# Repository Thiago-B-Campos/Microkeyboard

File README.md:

# Microkeyboard Hackpad

This is my hackpad project submission.

## Overview
I am making a micro keyboard in the QWERTY standard. The goal is to have at least 12 keys, 1 OLED display, and 1 rotary encoder.

## Images

### Schematic

### PCB

### Case

### Case - Shell

### BOM:

- 11x Cherry MX Switches
- 1x XIAO RP2040
- 11x Keycaps
- 1x Alps EC11E Rotary Encoder/Switch
- 4x M3x16mm screws
- 1x 3D Printed Case (2 parts)

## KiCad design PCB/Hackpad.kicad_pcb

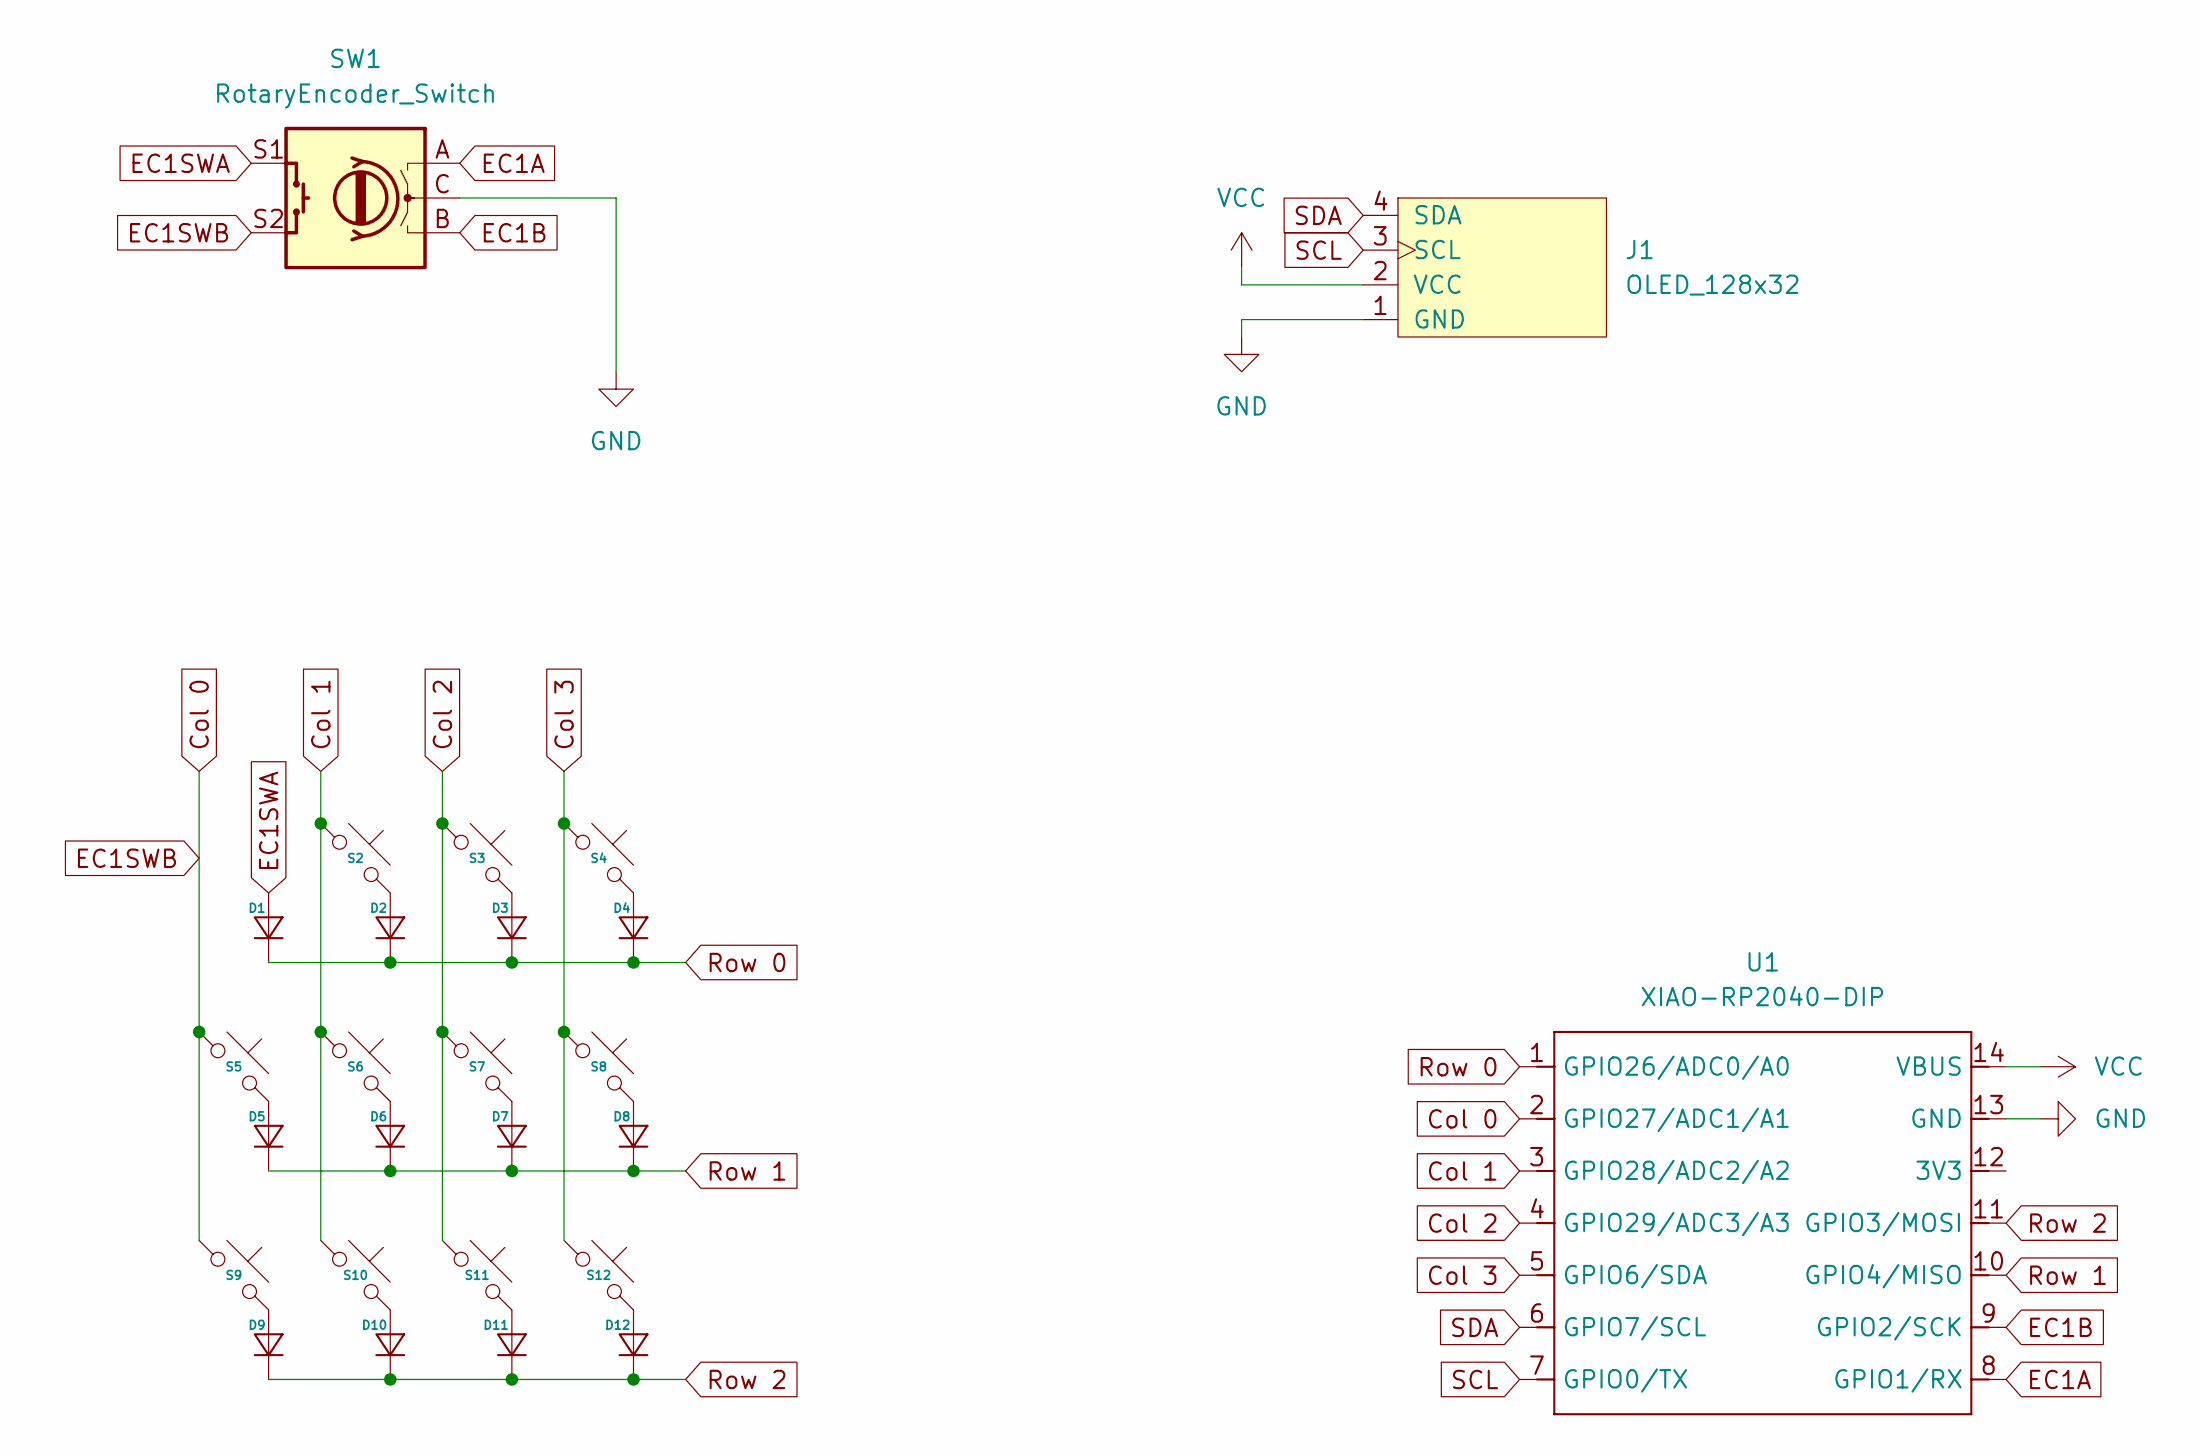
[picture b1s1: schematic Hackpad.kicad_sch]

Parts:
D1, D2, D3, D4, D5, D6, D7, D8, D9, D10, D11, D12: Diode_DO-35
J1: OLED_128x32
S2, S3, S4, S5, S6, S7, S8, S9, S10, S11, S12: SW_Cherry_MX_PCB_1.00u
SW1: RotaryEncoder_Switch; RotaryEncoder_Alps_EC11E-Switch_Vertical_H20mm
U1: XIAO-RP2040-DIP; Seeed_XIAO_RP2040

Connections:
Col 0: S5.1, S9.1, SW1.S2, U1.2 (GPIO27/ADC1/A1)
Col 1: S2.1, S6.1, S10.1, U1.3 (GPIO28/ADC2/A2)
Col 2: S3.1, S7.1, S11.1, U1.4 (GPIO29/ADC3/A3)
Col 3: S4.1, S8.1, S12.1, U1.5 (GPIO6/SDA)
EC1A: SW1.A, U1.8 (GPIO1/RX)
EC1B: SW1.B, U1.9 (GPIO2/SCK)
EC1SWA: D1.2 (A), SW1.S1
GND: J1.1 (GND), SW1.C, U1.13 (GND)
unnamed: D2.2 (A), S2.2
unnamed: D3.2 (A), S3.2
unnamed: D4.2 (A), S4.2
unnamed: D5.2 (A), S5.2
unnamed: D6.2 (A), S6.2
unnamed: D7.2 (A), S7.2
unnamed: D8.2 (A), S8.2
unnamed: D9.2 (A), S9.2
unnamed: D10.2 (A), S10.2
unnamed: D11.2 (A), S11.2
unnamed: D12.2 (A), S12.2
Row 0: D1.1 (K), D2.1 (K), D3.1 (K), D4.1 (K), U1.1 (GPIO26/ADC0/A0)
Row 1: D5.1 (K), D6.1 (K), D7.1 (K), D8.1 (K), U1.10 (GPIO4/MISO)
Row 2: D9.1 (K), D10.1 (K), D11.1 (K), D12.1 (K), U1.11 (GPIO3/MOSI)
SCL: J1.3 (SCL), U1.7 (GPIO0/TX)
SDA: J1.4 (SDA), U1.6 (GPIO7/SCL)
VCC: J1.2 (VCC), U1.14 (VBUS)

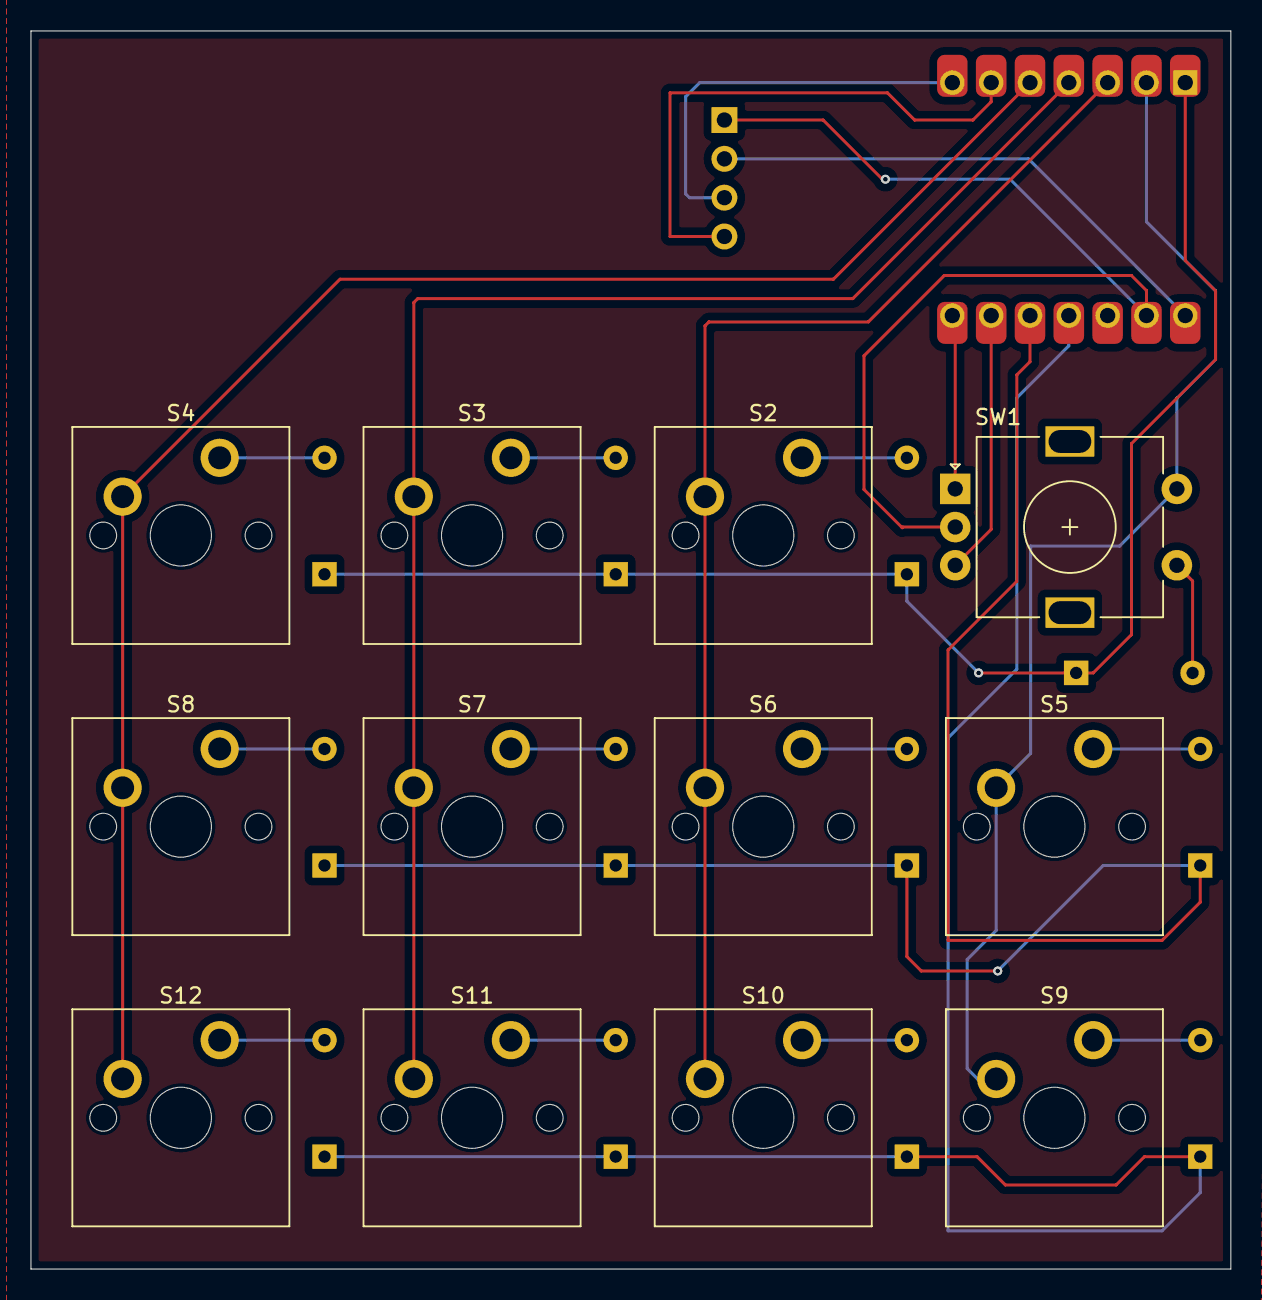
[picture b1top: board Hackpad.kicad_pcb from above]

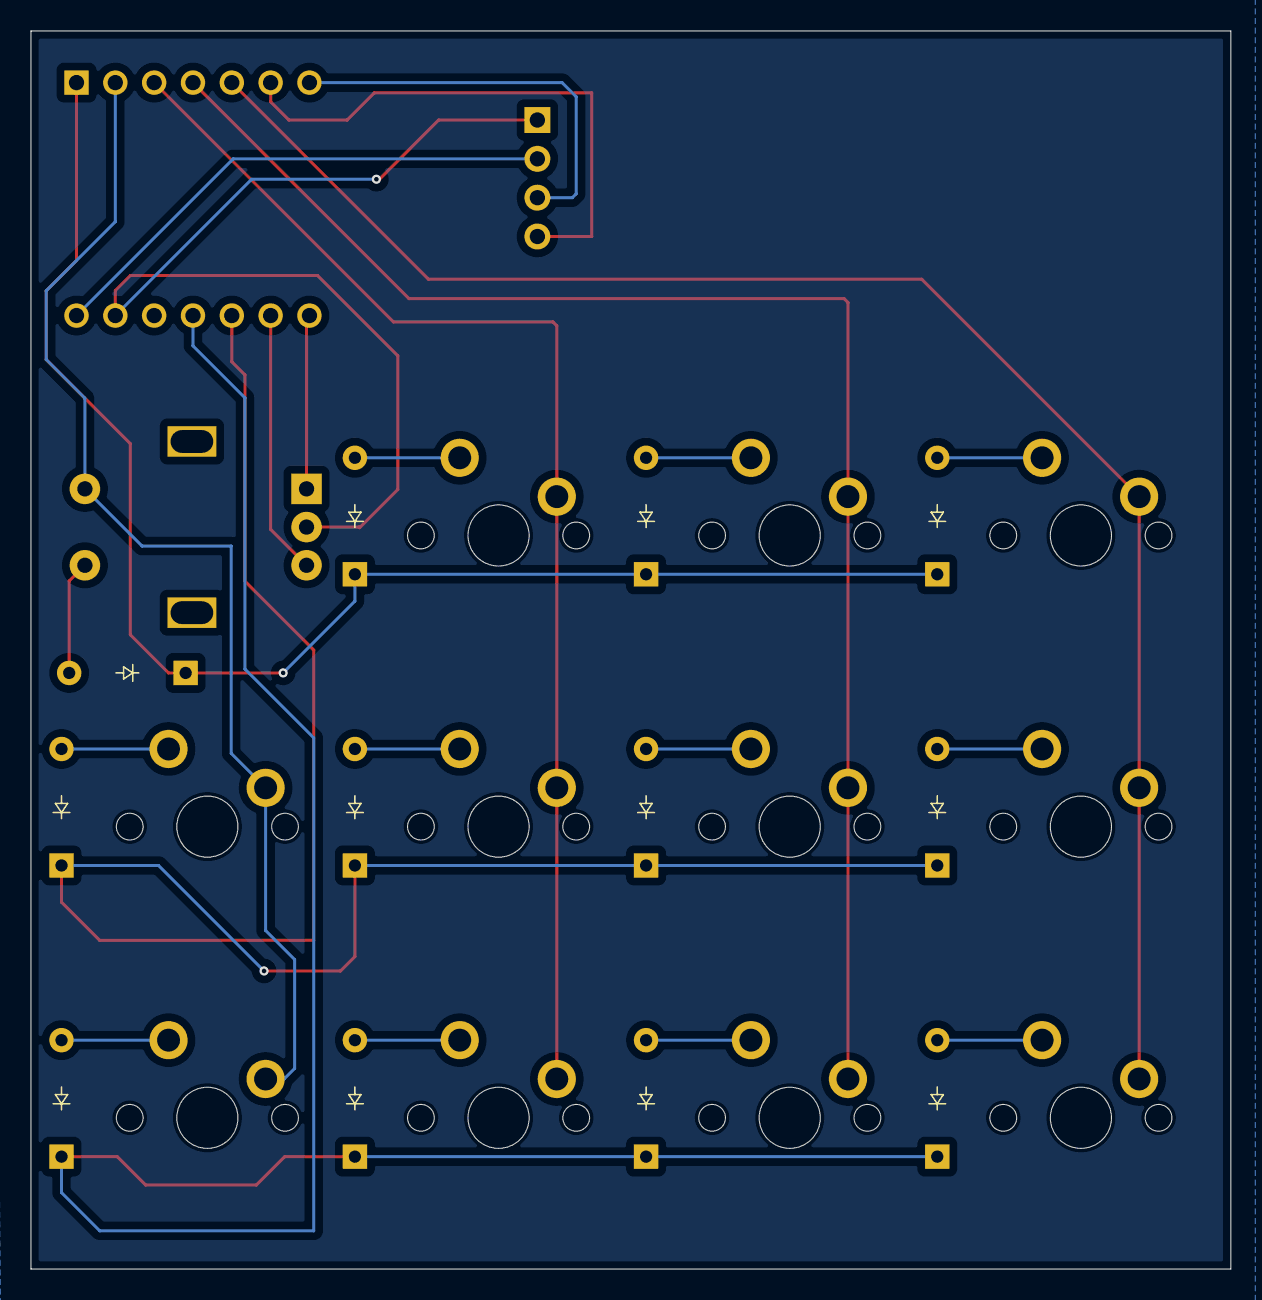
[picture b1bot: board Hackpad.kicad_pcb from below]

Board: 2 copper layers, 78.5 x 81.0 mm, 26 parts (12 on the bottom side), 25 nets.

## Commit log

2025-12-20 Create folder Firmware
2025-12-20 Add hackpad project files
